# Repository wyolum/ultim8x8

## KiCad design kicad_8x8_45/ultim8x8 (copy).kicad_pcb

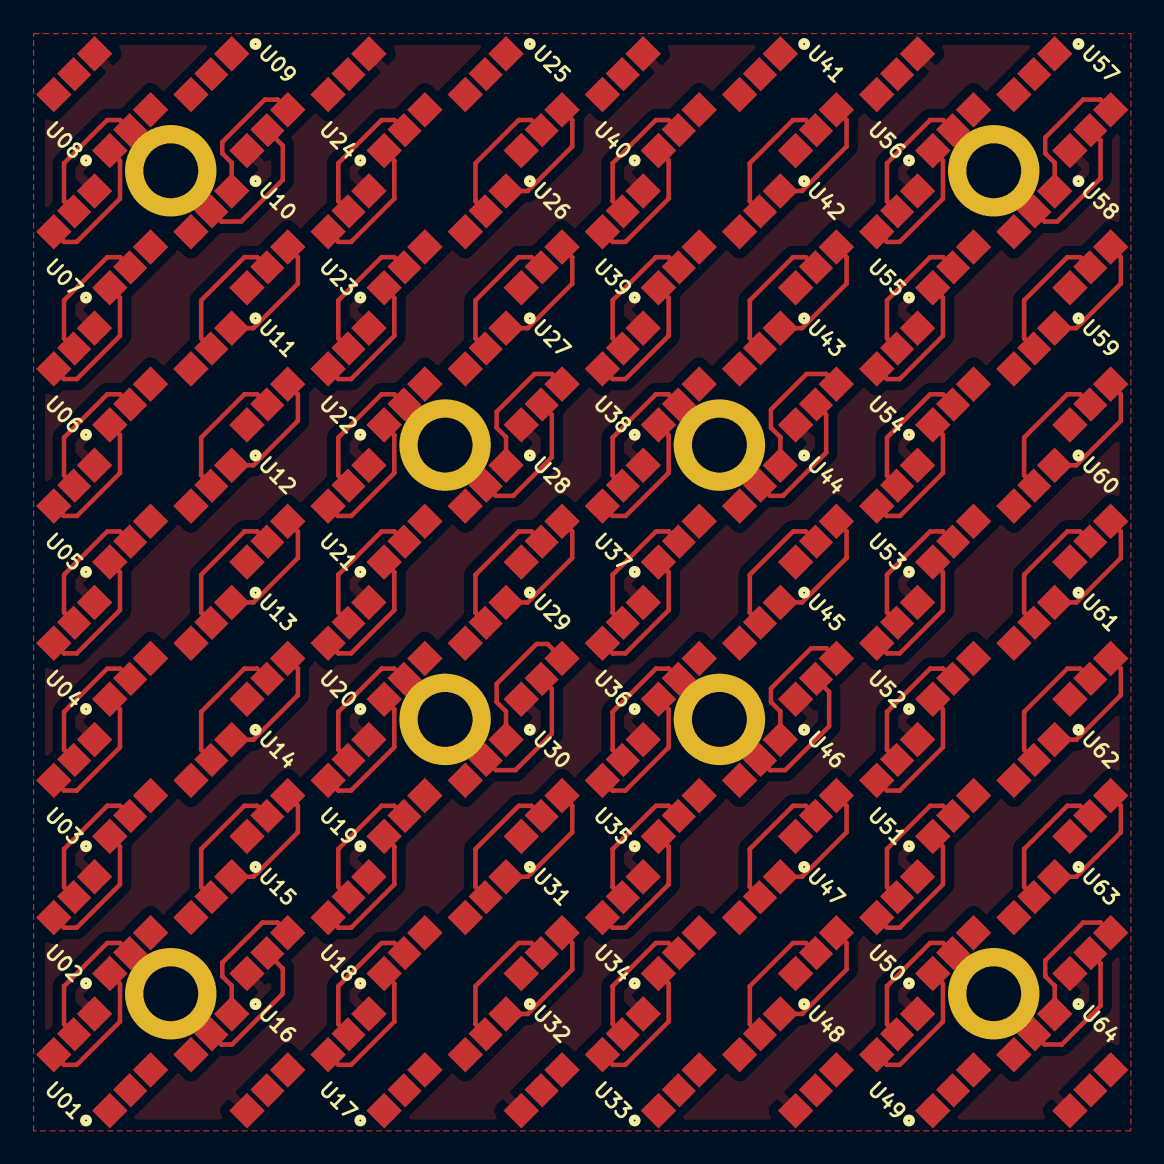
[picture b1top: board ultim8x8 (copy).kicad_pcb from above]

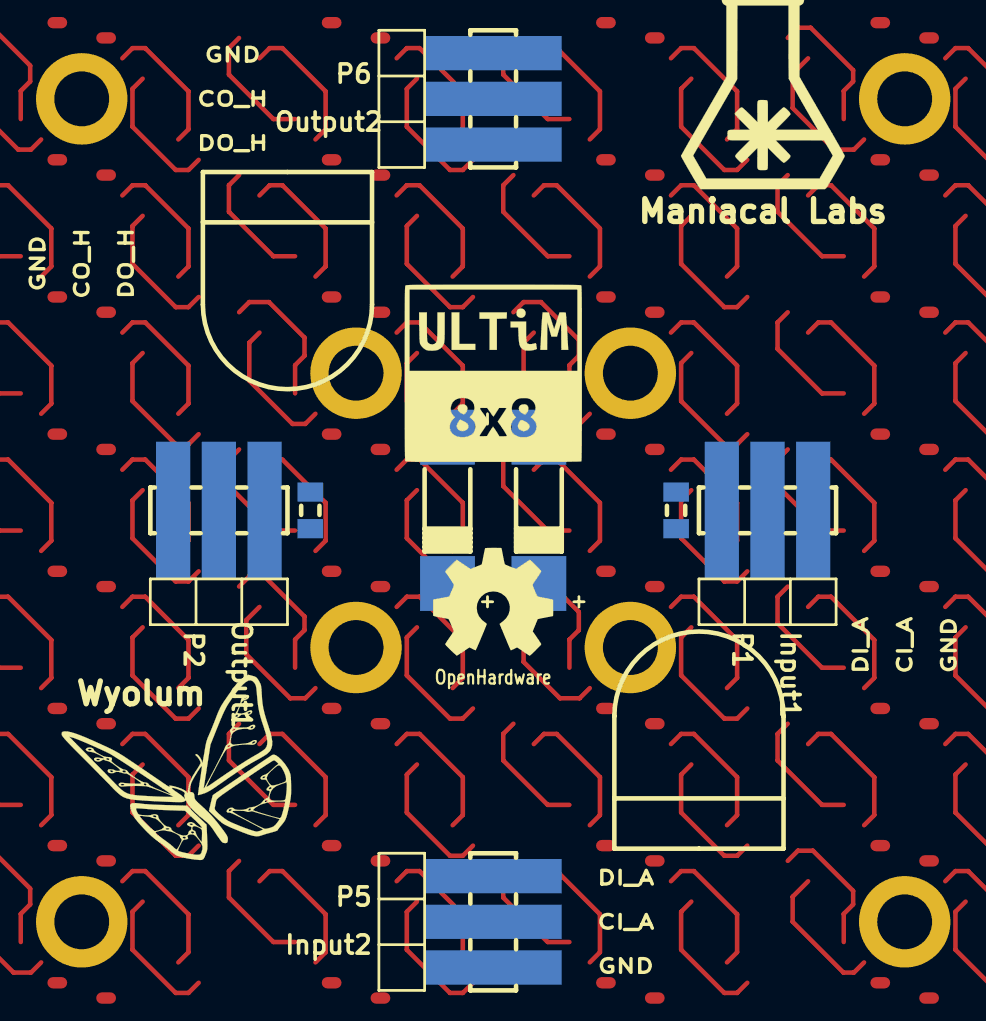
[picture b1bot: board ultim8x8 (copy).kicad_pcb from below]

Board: 2 copper layers, 84 parts (20 on the bottom side), 132 nets.

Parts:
C1, C3: 100nF; c_0805
C2, C4: 47uF 20V; c_2917
L1: ULTiM8x8; logo_ultim8x8
L2: OSHW; OSHW_6mm
L3: Wyolum; logo_wyo_butterfly
L4: Maniacal Labs; logo_MLlabs
P1: Input1; header_3pos_smd_male
P2: Output1; header_3pos_smd_male
P5: Input2; header_3pos_smd_male
P6: Output2; header_3pos_smd_male
S1, S1#2, S1#3, S1#4, S1#5, S1#6, S1#7, S1#8: CONN_1; Screw_SSide_2
U01, U02, U03, U04, U05, U06, U07, U08, U09, U10, U11, U12, U13, U14, U15, U16, U17, U18, U19, U20, U21, U22, U23, U24, U25, U26, U27, U28, U29, U30, U31, U32, U33, U34, U35, U36, U37, U38, U39, U40, U41, U42, U43, U44, U45, U46, U47, U48, U49, U50, U51, U52, U53, U54, U55, U56, U57, U58, U59, U60, U61, U62, U63, U64: APA102

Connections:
/Row_A/5V: C1.2, C2.1, C3.2, C4.1, U01.4, U02.4, U03.4, U04.4, U05.4, U06.4, U07.4, U08.4, U09.4, U10.4, U11.4, U12.4, U13.4, U14.4, U15.4, U16.4, U17.4, U18.4, U19.4, U20.4, U21.4, U22.4, U23.4, U24.4, U25.4, U26.4, U27.4, U28.4, U29.4, U30.4, U31.4, U32.4, U33.4, U34.4, U35.4, U36.4, U37.4, U38.4, U39.4, U40.4, U41.4, U42.4, U43.4, U44.4, U45.4, U46.4, U47.4, U48.4, U49.4, U50.4, U51.4, U52.4, U53.4, U54.4, U55.4, U56.4, U57.4, U58.4, U59.4, U60.4, U61.4, U62.4, U63.4, U64.4
/Row_A/CI_A: P1.2, P5.2, U01.2
/Row_A/CI_B: U08.5, U09.2
/Row_A/DI_A: P1.1, P5.1, U01.1
/Row_A/DI_B: U08.6, U09.1
/Row_B/CI_C: U16.5, U17.2
/Row_B/DI_C: U16.6, U17.1
/Row_C/CI_D: U24.5, U25.2
/Row_C/DI_D: U24.6, U25.1
/Row_D/CI_E: U32.5, U33.2
/Row_D/DI_E: U32.6, U33.1
/Row_E/CI_F: U40.5, U41.2
/Row_E/DI_F: U40.6, U41.1
/Row_F/CI_G: U48.5, U49.2
/Row_F/DI_G: U48.6, U49.1
/Row_G/CI_H: U56.5, U57.2
/Row_G/DI_H: U56.6, U57.1
/Row_H/CO_H: P2.2, P6.2, U64.5
/Row_H/DO_H: P2.3, P6.3, U64.6
GND: C1.1, C2.2, C3.1, C4.2, P1.3, P2.1, P5.3, P6.1, U01.3, U02.3, U03.3, U04.3, U05.3, U06.3, U07.3, U08.3, U09.3, U10.3, U11.3, U12.3, U13.3, U14.3, U15.3, U16.3, U17.3, U18.3, U19.3, U20.3, U21.3, U22.3, U23.3, U24.3, U25.3, U26.3, U27.3, U28.3, U29.3, U30.3, U31.3, U32.3, U33.3, U34.3, U35.3, U36.3, U37.3, U38.3, U39.3, U40.3, U41.3, U42.3, U43.3, U44.3, U45.3, U46.3, U47.3, U48.3, U49.3, U50.3, U51.3, U52.3, U53.3, U54.3, U55.3, U56.3, U57.3, U58.3, U59.3, U60.3, U61.3, U62.3, U63.3, U64.3
unnamed: U01.5, U02.2
unnamed: U01.6, U02.1
unnamed: U02.5, U03.2
unnamed: U02.6, U03.1
unnamed: U03.5, U04.2
unnamed: U03.6, U04.1
unnamed: U04.5, U05.2
unnamed: U04.6, U05.1
unnamed: U05.5, U06.2
unnamed: U05.6, U06.1
unnamed: U06.5, U07.2
unnamed: U06.6, U07.1
unnamed: U07.5, U08.2
unnamed: U07.6, U08.1
unnamed: U09.5, U10.2
unnamed: U09.6, U10.1
unnamed: U10.5, U11.2
unnamed: U10.6, U11.1
unnamed: U11.5, U12.2
unnamed: U11.6, U12.1
unnamed: U12.5, U13.2
unnamed: U12.6, U13.1
unnamed: U13.5, U14.2
unnamed: U13.6, U14.1
unnamed: U14.5, U15.2
unnamed: U14.6, U15.1
unnamed: U15.5, U16.2
unnamed: U15.6, U16.1
unnamed: U17.5, U18.2
unnamed: U17.6, U18.1
unnamed: U18.5, U19.2
unnamed: U18.6, U19.1
unnamed: U19.5, U20.2
unnamed: U19.6, U20.1
unnamed: U20.5, U21.2
unnamed: U20.6, U21.1
unnamed: U21.5, U22.2
unnamed: U21.6, U22.1
unnamed: U22.5, U23.2
unnamed: U22.6, U23.1
unnamed: U23.5, U24.2
unnamed: U23.6, U24.1
unnamed: U25.5, U26.2
unnamed: U25.6, U26.1
unnamed: U26.5, U27.2
unnamed: U26.6, U27.1
unnamed: U27.5, U28.2
unnamed: U27.6, U28.1
unnamed: U28.5, U29.2
unnamed: U28.6, U29.1
unnamed: U29.5, U30.2
unnamed: U29.6, U30.1
unnamed: U30.5, U31.2
unnamed: U30.6, U31.1
unnamed: U31.5, U32.2
unnamed: U31.6, U32.1
unnamed: U33.5, U34.2
unnamed: U33.6, U34.1
unnamed: U34.5, U35.2
unnamed: U34.6, U35.1
unnamed: U35.5, U36.2
unnamed: U35.6, U36.1
unnamed: U36.5, U37.2
unnamed: U36.6, U37.1
unnamed: U37.5, U38.2
unnamed: U37.6, U38.1
unnamed: U38.5, U39.2
unnamed: U38.6, U39.1
unnamed: U39.5, U40.2
unnamed: U39.6, U40.1
unnamed: U41.5, U42.2
unnamed: U41.6, U42.1
unnamed: U42.5, U43.2
unnamed: U42.6, U43.1
unnamed: U43.5, U44.2
unnamed: U43.6, U44.1
unnamed: U44.5, U45.2
unnamed: U44.6, U45.1
unnamed: U45.5, U46.2
unnamed: U45.6, U46.1
unnamed: U46.5, U47.2
unnamed: U46.6, U47.1
unnamed: U47.5, U48.2
unnamed: U47.6, U48.1
unnamed: U49.5, U50.2
unnamed: U49.6, U50.1
unnamed: U50.5, U51.2
unnamed: U50.6, U51.1
unnamed: U51.5, U52.2
unnamed: U51.6, U52.1
unnamed: U52.5, U53.2
unnamed: U52.6, U53.1
unnamed: U53.5, U54.2
unnamed: U53.6, U54.1
unnamed: U54.5, U55.2
unnamed: U54.6, U55.1
unnamed: U55.5, U56.2
unnamed: U55.6, U56.1
unnamed: U57.5, U58.2
unnamed: U57.6, U58.1
unnamed: U58.5, U59.2
unnamed: U58.6, U59.1
unnamed: U59.5, U60.2
unnamed: U59.6, U60.1
unnamed: U60.5, U61.2
unnamed: U60.6, U61.1
unnamed: U61.5, U62.2
unnamed: U61.6, U62.1
unnamed: U62.5, U63.2
unnamed: U62.6, U63.1
unnamed: U63.5, U64.2
unnamed: U63.6, U64.1

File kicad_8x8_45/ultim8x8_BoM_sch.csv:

Reference, Value, Footprint, Datasheet, Field4, Field5, Field6, manf#, Field7, Field8, Field9, Field10, Field11
L2,OSHW,ultim8x8_libs:OSHW_6mm,
L3,Wyolum,ultim8x8_libs:logo_wyo_butterfly,
P1,Input1,ultim8x8_libs:header_3pos_th_male,,CONN HEADER 50POS .100" SGL GOLD,Header, Unshrouded, Male pin,,0.1",,,,,,
P2,Output1,ultim8x8_libs:header_3pos_th_male,,CONN HEADER 50POS .100" SGL GOLD,Header, Unshrouded, Male pin,,0.1",,,,,,
P5,Input2,ultim8x8_libs:header_3pos_th_male,,CONN HEADER 50POS .100" SGL GOLD,Header, Unshrouded, Male pin,,0.1",,,,,,
P6,Output2,ultim8x8_libs:header_3pos_th_male,,CONN HEADER 50POS .100" SGL GOLD,Header, Unshrouded, Male pin,,0.1",,,,,,
P3,5V,ultim8x8_libs:Screw,,,,,mfr_pn,,,,,
P4,GND,ultim8x8_libs:Screw,,,,,mfr_pn,,,,,
L4,Maniacal Labs,ultim8x8_libs:logo_MLlabs,
L1,ULTiM8x8,ultim8x8_libs:logo_ultim8x8,
P11,5V,ultim8x8_libs:Screw,,,,,mfr_pn,,,,,
P12,GND,ultim8x8_libs:Screw,,,,,mfr_pn,,,,,
P8,CO_H,ultim8x8_libs:Screw,,,,,mfr_pn,,,,,
P9,DI_A,ultim8x8_libs:Screw,,,,,mfr_pn,,,,,
P7,CI_A,ultim8x8_libs:Screw,,,,,mfr_pn,,,,,
P10,DO_H,ultim8x8_libs:Screw,,,,,mfr_pn,,,,,
U57,APA102,ultim8x8_libs:APA102,,,,,mfr_pn,,,,,
C3,100nF,ultim8x8_libs:c_0805,,CAP CER 0.1UF 25V 10% X7R 0805,100nF, 25V,Surface Mount, MLCC,Value,Kemet,C0805C104K3RACTU,Digikey,399-1168-1-ND,http://www.digikey.com/product-detail/en/C0805C104K3RACTU/39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
C4,47uF 20V,ultim8x8_libs:c_2917,,CAP ALUM 47UF 8V 20% SMD,47u,8V,2917 (7343 Metric),Value,Panasonic Electronic Components,EEF-CD0K470R,Digikey,PCE3606CT-ND,http://www.digikey.com/product-detail/en/EEF-CD0K470R/PCE360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
U58,APA102,ultim8x8_libs:APA102,,,,,mfr_pn,,,,,
U59,APA102,ultim8x8_libs:APA102,,,,,mfr_pn,,,,,
U60,APA102,ultim8x8_libs:APA102,,,,,mfr_pn,,,,,
U61,APA102,ultim8x8_libs:APA102,,,,,mfr_pn,,,,,
U62,APA102,ultim8x8_libs:APA102,,,,,mfr_pn,,,,,
U63,APA102,ultim8x8_libs:APA102,,,,,mfr_pn,,,,,
U64,APA102,ultim8x8_libs:APA102,,,,,mfr_pn,,,,,
U49,APA102,ultim8x8_libs:APA102,,,,,mfr_pn,,,,,
U50,APA102,ultim8x8_libs:APA102,,,,,mfr_pn,,,,,
U51,APA102,ultim8x8_libs:APA102,,,,,mfr_pn,,,,,
U52,APA102,ultim8x8_libs:APA102,,,,,mfr_pn,,,,,
U53,APA102,ultim8x8_libs:APA102,,,,,mfr_pn,,,,,
U54,APA102,ultim8x8_libs:APA102,,,,,mfr_pn,,,,,
U55,APA102,ultim8x8_libs:APA102,,,,,mfr_pn,,,,,
U56,APA102,ultim8x8_libs:APA102,,,,,mfr_pn,,,,,
U41,APA102,ultim8x8_libs:APA102,,,,,mfr_pn,,,,,
U42,APA102,ultim8x8_libs:APA102,,,,,mfr_pn,,,,,
U43,APA102,ultim8x8_libs:APA102,,,,,mfr_pn,,,,,
U44,APA102,ultim8x8_libs:APA102,,,,,mfr_pn,,,,,
U45,APA102,ultim8x8_libs:APA102,,,,,mfr_pn,,,,,
U46,APA102,ultim8x8_libs:APA102,,,,,mfr_pn,,,,,
U47,APA102,ultim8x8_libs:APA102,,,,,mfr_pn,,,,,
U48,APA102,ultim8x8_libs:APA102,,,,,mfr_pn,,,,,
U33,APA102,ultim8x8_libs:APA102,,,,,mfr_pn,,,,,
U34,APA102,ultim8x8_libs:APA102,,,,,mfr_pn,,,,,
U35,APA102,ultim8x8_libs:APA102,,,,,mfr_pn,,,,,
U36,APA102,ultim8x8_libs:APA102,,,,,mfr_pn,,,,,
U37,APA102,ultim8x8_libs:APA102,,,,,mfr_pn,,,,,
U38,APA102,ultim8x8_libs:APA102,,,,,mfr_pn,,,,,
U39,APA102,ultim8x8_libs:APA102,,,,,mfr_pn,,,,,
U40,APA102,ultim8x8_libs:APA102,,,,,mfr_pn,,,,,
U25,APA102,ultim8x8_libs:APA102,,,,,mfr_pn,,,,,
U26,APA102,ultim8x8_libs:APA102,,,,,mfr_pn,,,,,
U27,APA102,ultim8x8_libs:APA102,,,,,mfr_pn,,,,,
U28,APA102,ultim8x8_libs:APA102,,,,,mfr_pn,,,,,
U29,APA102,ultim8x8_libs:APA102,,,,,mfr_pn,,,,,
U30,APA102,ultim8x8_libs:APA102,,,,,mfr_pn,,,,,
U31,APA102,ultim8x8_libs:APA102,,,,,mfr_pn,,,,,
U32,APA102,ultim8x8_libs:APA102,,,,,mfr_pn,,,,,
U17,APA102,ultim8x8_libs:APA102,,,,,mfr_pn,,,,,
U18,APA102,ultim8x8_libs:APA102,,,,,mfr_pn,,,,,
U19,APA102,ultim8x8_libs:APA102,,,,,mfr_pn,,,,,
U20,APA102,ultim8x8_libs:APA102,,,,,mfr_pn,,,,,
U21,APA102,ultim8x8_libs:APA102,,,,,mfr_pn,,,,,
U22,APA102,ultim8x8_libs:APA102,,,,,mfr_pn,,,,,
U23,APA102,ultim8x8_libs:APA102,,,,,mfr_pn,,,,,
U24,APA102,ultim8x8_libs:APA102,,,,,mfr_pn,,,,,
U09,APA102,ultim8x8_libs:APA102,,,,,mfr_pn,,,,,
U10,APA102,ultim8x8_libs:APA102,,,,,mfr_pn,,,,,
U11,APA102,ultim8x8_libs:APA102,,,,,mfr_pn,,,,,
U12,APA102,ultim8x8_libs:APA102,,,,,mfr_pn,,,,,
U13,APA102,ultim8x8_libs:APA102,,,,,mfr_pn,,,,,
U14,APA102,ultim8x8_libs:APA102,,,,,mfr_pn,,,,,
U15,APA102,ultim8x8_libs:APA102,,,,,mfr_pn,,,,,
U16,APA102,ultim8x8_libs:APA102,,,,,mfr_pn,,,,,
C1,100nF,ultim8x8_libs:c_0805,,CAP CER 0.1UF 25V 10% X7R 0805,100nF, 25V,Surface Mount, MLCC,,Kemet,C0805C104K3RACTU,Digikey,399-1168-1-ND,http://www.digikey.com/product-detail/en/C0805C104K3RACTU/39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
C2,47uF 20V,ultim8x8_libs:c_2917,,CAP ALUM 47UF 8V 20% SMD,47u,8V,2917 (7343 Metric),Value,Panasonic Electronic Components,EEF-CD0K470R,Digikey,PCE3606CT-ND,http://www.digikey.com/product-detail/en/EEF-CD0K470R/PCE360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
U01,APA102,ultim8x8_libs:APA102,,,,,mfr_pn,,,,,
U02,APA102,ultim8x8_libs:APA102,,,,,mfr_pn,,,,,
U03,APA102,ultim8x8_libs:APA102,,,,,mfr_pn,,,,,
U04,APA102,ultim8x8_libs:APA102,,,,,mfr_pn,,,,,
U05,APA102,ultim8x8_libs:APA102,,,,,mfr_pn,,,,,
U06,APA102,ultim8x8_libs:APA102,,,,,mfr_pn,,,,,
U07,APA102,ultim8x8_libs:APA102,,,,,mfr_pn,,,,,
U08,APA102,ultim8x8_libs:APA102,,,,,mfr_pn,,,,,

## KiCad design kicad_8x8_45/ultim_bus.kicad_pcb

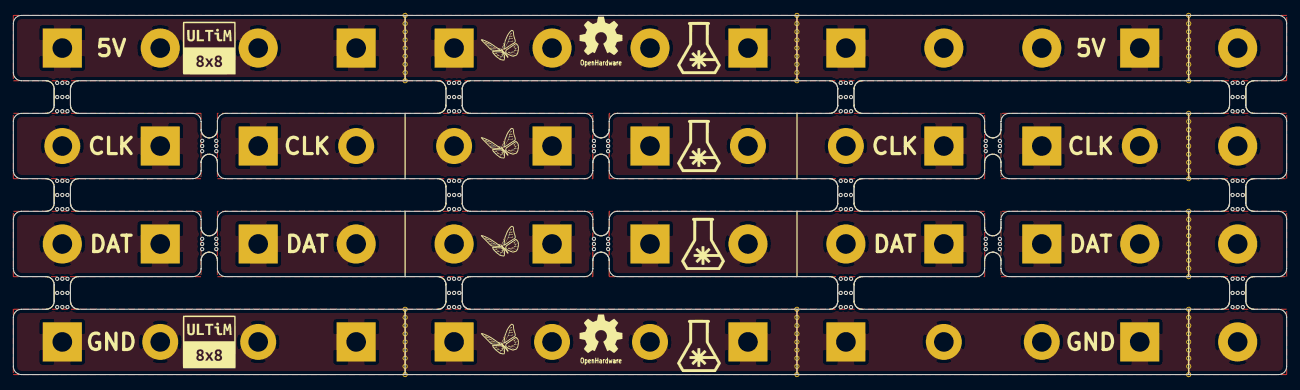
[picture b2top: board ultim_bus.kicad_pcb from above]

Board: 2 copper layers, 198.1 x 55.9 mm, 82 parts (0 on the bottom side), 10 nets.

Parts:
L1, L2: OSHW; OSHW_6mm
L3, L4, L5, L6: WyoLum; logo_wyo_butterfly_small
L7, L8, L9, L10: Maniacal; logo_MLlabs_small
L11, L12: ULTiM; logo_ultim8x8_small
M1, M2, M3, M4, M8, M9, M10, M11, M15, M16, M17, M18: MouseBite; mouse-bite-5.08mm-slot
M5, M6, M7, M12, M13, M14: MouseBite; mouse-bite-2.54mm-slot
P1, P4, P5, P8, P9, P12, P15, P16, P19, P20, P23, P24, P28, P29, P32, P33, P36, P37, P40, P43, P44, P47, P48, P51: CONN_1; Screw_SqPad
P2, P3, P6, P7, P10, P11, P13, P14, P17, P18, P21, P22, P25, P26, P27, P30, P31, P34, P35, P38, P39, P41, P42, P45, P46, P49, P50, P52: CONN_1; Screw

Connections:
/ROW1: P1.1, P2.1, P3.1, P4.1, P5.1, P6.1, P7.1, P8.1, P9.1, P10.1, P11.1, P12.1, P13.1
/ROW2: P40.1, P41.1, P42.1, P43.1, P44.1, P45.1, P46.1, P47.1, P48.1, P49.1, P50.1, P51.1, P52.1
/ROW31: P14.1, P15.1
/ROW32: P16.1, P17.1, P18.1, P19.1
/ROW33: P20.1, P21.1, P22.1, P23.1
/ROW34: P24.1, P25.1, P26.1
/ROW41: P27.1, P28.1
/ROW42: P29.1, P30.1, P31.1, P32.1
/ROW43: P33.1, P34.1, P35.1, P36.1
/ROW44: P37.1, P38.1, P39.1
